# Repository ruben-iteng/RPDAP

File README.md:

<div align="center">

# RPDAP

<br/>

CMSIS-DAP debugger hardware based on a Raspberry Pi RP2040 microcontroller.

</div>

## About

This project contains the hardware designs for a RP2040 based CMSIS-DAP debugger running the [free-dap](https://github.com/ruben-iteng/free-dap) firmware.

This project is build with [atopile](https://atopile.io).

### Features

- USB interface (data and power)
- status LEDs for VCP (Virtual COM Port), DAP status, and power.
- level shifted target interface (SWD, UART)
  - 1.2-5.5V target logic voltage

#### Layouts

There are various layouts and standalone boards available:

|   |   |
|---------------------------------------|---------------------------------------|
| Basic layout without connectors (for inclusion in your own design/PCBA) | Standalone stick shaped layout with female USB Type-C, Cortex-M debug header and 4-pin JST-SH UART connector. All inside a PCB enclosure. |
|    |  |
| Standalone RPDAP Compact board (JLink Base Compact compatible board shape) |  JLink Base Compact compatible "footprint" (for using as build-in debugger/programmer) |

### Firmware

The firmware for the debugger is available in the [free-dap](https://github.com/ruben-iteng/free-dap/releases/latest) repository.
Follow this standard RP2040 flashing procedure to flash the firmware.

### Enclosures

This RPDAP Stick has a build in enclosure in the design (part of the PCB), and the RPDAP Compact board has a [3D printable enclosure](./cad/README.md) available.

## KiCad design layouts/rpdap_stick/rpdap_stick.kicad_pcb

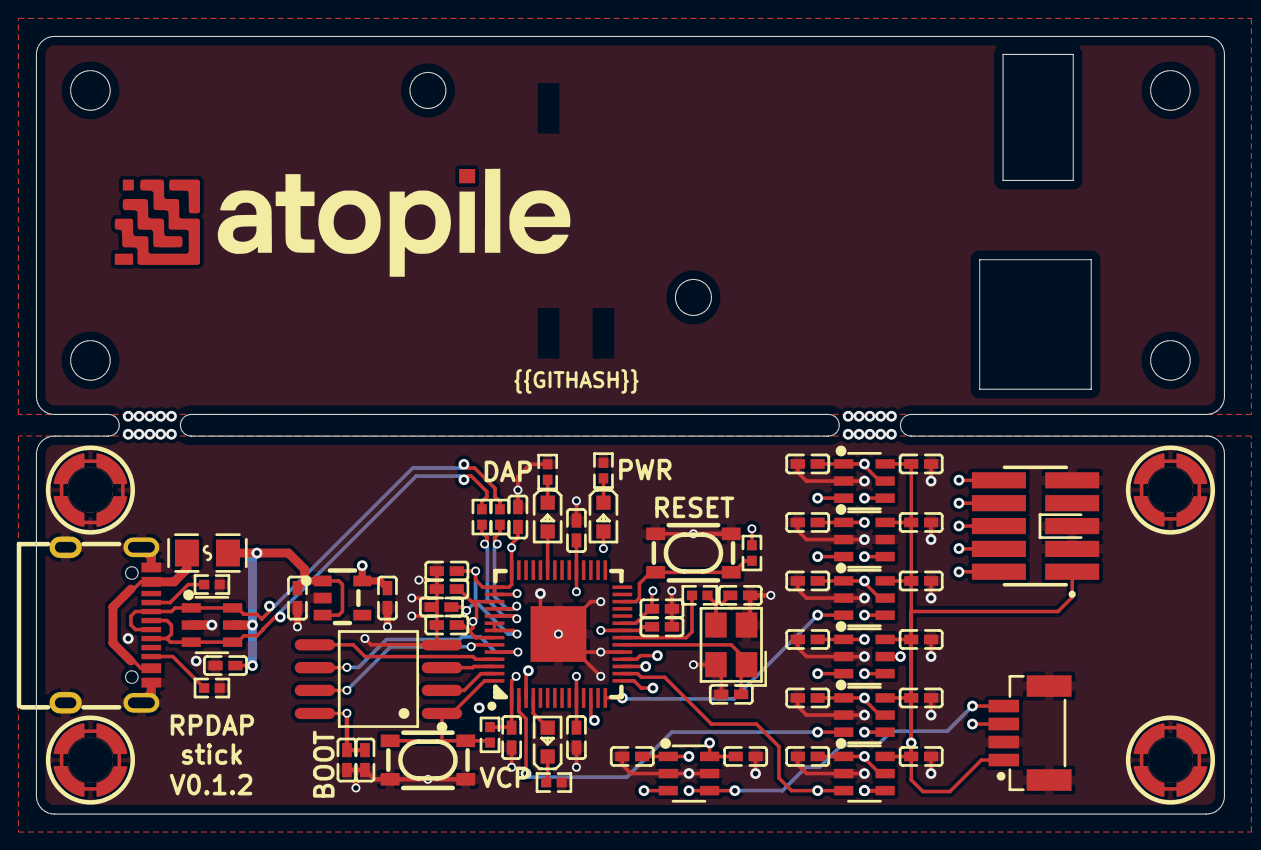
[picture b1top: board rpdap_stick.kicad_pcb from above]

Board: 4 copper layers, 66.0 x 43.2 mm, 67 parts (0 on the bottom side), 42 nets.

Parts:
C1, C2, C3, C4, C5, C6, C7, C8, C9, C10, C11, C12, C13, C14, C15, C16, C18, C19, C23, C24, C25, C26, C27, C28, C30, C31: 100nF ±10% 16V X7R; C0402
C17, C22, C29: 2.2µF ±10% 16V X5R; C0402
C20, C21: 15pF ±5% 50V C0G; C0402
CN1: CONN-SMD_FTSH-105-01-L-DV-K-TR
D1: SOT-23-6_L2.9-W1.6-P0.95-LS2.8-BL
F1: F0805
LED1, LED2, LED3: LED0603-RD
LOGO1: atopile_Logo_25x6mm
R1, R3, R4, R8: 10kΩ ±1% 62.5mW; R0402
R2, R7: 1kΩ ±1% 62.5mW; R0402
R5, R6: 27Ω ±1% 62.5mW; R0402
R9, R10: 5.1kΩ ±1% 62.5mW; R0402
SW1, SW2: KEY-SMD_4P-L4.2-W3.2-P2.20-LS4.6
U1: SOT-23-5_L2.9-W1.6-P0.95-LS2.8-BR
U2, U3, U4, U5, U6, U7, U15: SOT-23-6_L2.9-W1.6-P0.95-LS2.8-BL
U8: LQFN-56_L7.0-W7.0-P0.4-EP
U9: SOIC-8_L5.3-W5.3-P1.27-LS8.0-BL
U10: CONN-SMD_4P-P1.00_HC-1.0-4PLT
U11, U12, U13, U14: SMD_BD3.2-D2.4
USB1: USB-C-SMD_TYPE-C-6PIN-2MD-073
X1: CRYSTAL-SMD_4P-L3.2-W2.5-BL

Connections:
3V3: C2.1, C3.1, C5.1, C7.1, C9.1, C11.1, C13.1, C15.1, C22.1, C23.1, C24.1, C25.1, C26.1, C27.1, C28.1, C29.1, C30.1, LED2.2, R1.2, R4.2, U1.5, U2.1, U3.1, U3.5, U4.1, U5.1, U5.5, U6.1, U6.5, U7.1, U7.5, U8.1, U8.10, U8.22, U8.33, U8.42, U8.43, U8.44, U8.48, U8.49, U9.8, U15.1
DIR: U2.5, U8.12
GND: C1.2, C2.2, C3.2, C4.2, C5.2, C6.2, C7.2, C8.2, C9.2, C10.2, C11.2, C12.2, C13.2, C14.2, C15.2, C16.2, C17.2, C18.2, C19.2, C20.2, C21.2, C22.2, C23.2, C24.2, C25.2, C26.2, C27.2, C28.2, C29.2, C30.2, C31.2, CN1.3, CN1.5, CN1.9, D1.2, R3.1, R7.2, R8.2, R9.2, R10.2, SW1.3, SW1.4, SW2.3, SW2.4, U1.2, U2.2, U3.2, U4.2, U4.5, U5.2, U6.2, U7.2, U8.19, U8.57, U9.4, U10.2, U10.5, U10.6, U11.1, U12.1, U13.1, U14.1, U15.2, U15.5, USB1.1, USB1.12, USB1.13, USB1.14, USB1.15, USB1.16, X1.2, X1.4
K: LED1.1, R3.2
RUN: R4.1, SW2.1, SW2.2, U8.26
TCK_SWCLK: CN1.4, U3.4
TDI: CN1.8, U6.4
TDO_SWO: CN1.6, U4.4
TMS_DIO: CN1.2, U2.4
Vbus_fused: C1.1, C31.1, D1.5, F1.2, U1.1, U1.3
XIN: C20.1, U8.20, X1.1
XOUT: R2.2, U8.21
_core_regulator_out_power-VCC: C17.1, C18.1, C19.1, U8.23, U8.45, U8.50
anode: LED3.2, U8.4
cc[0]-line: R9.1, USB1.4
cc[1]-line: R10.1, USB1.10
chip_select: R1.1, SW1.1, SW1.2, U8.56, U9.1
clock: U8.52, U9.6
data_0: U8.53, U9.5
data_1: U8.55, U9.2
data_2: U8.54, U9.3
data_3: U8.51, U9.7
footprint-cathode-0: LED2.1, R7.1
footprint-cathode-1: LED3.1, R8.1
gpio[11]-A: U3.3, U8.14
gpio[12]-A: U2.3, U8.15
gpio[13]-A: U6.3, U8.16
gpio[14]-A: U4.3, U8.17
gpio[15]-A: U5.3, U8.18
input-A: LED1.2, U8.37
input-USB_D_N: D1.1, D1.6, R6.1, USB1.5, USB1.7
input-USB_D_P: D1.3, D1.4, R5.1, USB1.6, USB1.8
mcu-uart-RX: U8.3, U15.3
mcu-uart-TX: U7.3, U8.2
nRESET: CN1.10, U5.4
output: C21.1, R2.1, X1.3
output-USB_D_N: R6.2, U8.46
output-USB_D_P: R5.2, U8.47
power_vbus-VCC: F1.1, USB1.2, USB1.11
reference-VCC: C4.1, C6.1, C8.1, C10.1, C12.1, C14.1, C16.1, CN1.1, U2.6, U3.6, U4.6, U5.6, U6.6, U7.6, U10.1, U15.6
uart_connector-uart-RX: U10.4, U15.4
uart_connector-uart-TX: U7.4, U10.3

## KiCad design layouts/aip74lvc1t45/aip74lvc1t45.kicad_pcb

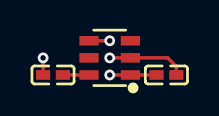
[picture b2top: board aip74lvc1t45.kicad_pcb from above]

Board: 2 copper layers, 3 parts (0 on the bottom side), 3 nets.

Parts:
C1, C2: 100nF ±10% 16V X7R; C0402
U1: SOT-23-6_L2.9-W1.6-P0.95-LS2.8-BL

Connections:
GND: C1.2, C2.2, U1.2
power_a-VCC: C1.1, U1.1
power_b-VCC: C2.1, U1.6

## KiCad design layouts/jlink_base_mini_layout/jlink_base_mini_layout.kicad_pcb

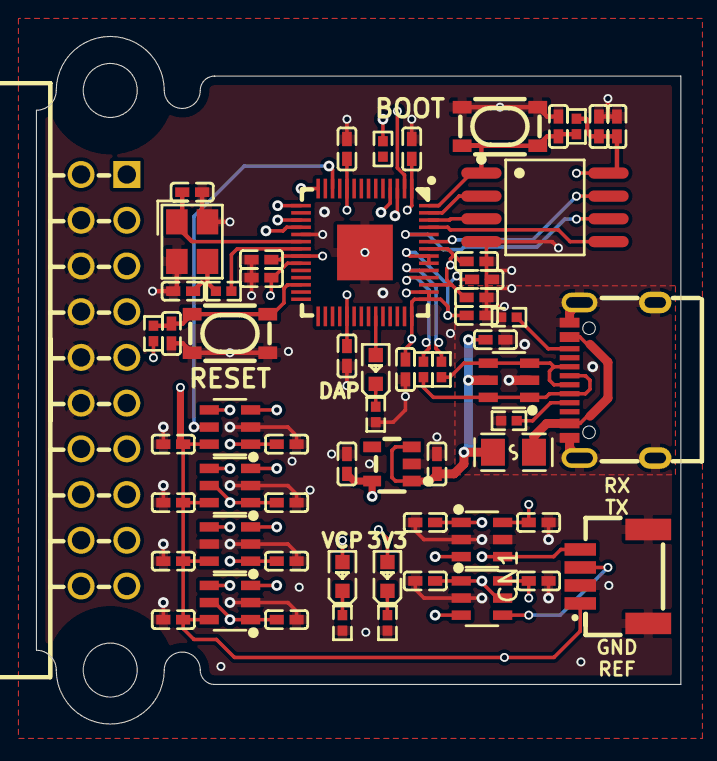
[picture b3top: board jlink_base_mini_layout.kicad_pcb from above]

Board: 4 copper layers, 35.8 x 38.2 mm, 62 parts (0 on the bottom side), 40 nets.

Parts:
C1, C2, C3, C4, C5, C6, C7, C8, C9, C10, C11, C12, C13, C14, C17, C18, C22, C23, C24, C25, C26, C27, C29, C31: 100nF ±10% 16V X7R; C0402
C15, C30: 1µF ±10% 25V X5R; C0402
C16, C21, C28: 2.2µF ±20% 6.3V X5R; C0402
C19, C20: 15pF ±5% 50V C0G; C0402
CN1: CONN-SMD_4P-P1.00_HCTL_HC-1.0-4PWT
D1: SOT-23-6_L2.9-W1.6-P0.95-LS2.8-BL
F1: F0805
LED1, LED2, LED3: LED0603-RD
R1, R4: 1kΩ ±1% 62.5mW; R0402
R2: 100kΩ ±1% 62.5mW; R0402
R3, R5, R6, R11: 10kΩ ±1% 62.5mW; R0402
R7, R8: 27Ω ±1% 62.5mW; R0402
R9, R10: 5.1kΩ ±1% 62.5mW; R0402
SW1, SW2: KEY-SMD_4P-L4.2-W3.2-P2.20-LS4.6
U1: IDC-TH_20P-P2.54_ZX-IDC2.54-2-10PWZ
U2: SOT-23-5_L2.9-W1.6-P0.95-LS2.8-BR
U3, U4, U5, U6, U7, U8: SOT-23-6_L2.9-W1.6-P0.95-LS2.8-BL
U9: LQFN-56_L7.0-W7.0-P0.4-EP
U10: SOIC-8_L5.3-W5.3-P1.27-LS8.0-BL
USB1: USB-C-SMD_TYPE-C-6PIN-2MD-073
X1: CRYSTAL-SMD_4P-L3.2-W2.5-BL

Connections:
3V3: C2.1, C3.1, C5.1, C7.1, C9.1, C11.1, C13.1, C21.1, C22.1, C23.1, C24.1, C25.1, C26.1, C27.1, C28.1, C29.1, LED1.2, R2.2, R3.1, R6.1, U2.5, U3.1, U4.1, U4.5, U5.1, U6.1, U6.5, U7.1, U7.5, U8.1, U9.1, U9.10, U9.22, U9.33, U9.42, U9.43, U9.44, U9.48, U9.49, U10.8
-hv: C4.1, C6.1, C8.1, C10.1, C12.1, C14.1, CN1.1, U1.1, U3.6, U4.6, U5.6, U6.6, U7.6, U8.6
A: LED2.2, U9.37
DI: U9.53, U10.5
DO: U9.55, U10.2
DVDD: C16.1, C17.1, C18.1, U9.23, U9.45, U9.50
GND: C1.2, C2.2, C3.2, C4.2, C5.2, C6.2, C7.2, C8.2, C9.2, C10.2, C11.2, C12.2, C13.2, C14.2, C15.2, C16.2, C17.2, C18.2, C19.2, C20.2, C21.2, C22.2, C23.2, C24.2, C25.2, C26.2, C27.2, C28.2, C29.2, C30.2, C31.2, CN1.2, CN1.5, CN1.6, D1.2, R1.2, R5.1, R9.2, R10.2, R11.2, SW1.1, SW1.2, SW2.1, SW2.2, U1.4, U1.6, U1.8, U1.10, U1.12, U2.2, U3.2, U4.2, U5.2, U5.5, U6.2, U7.2, U8.2, U8.5, U9.19, U9.57, U10.4, USB1.1, USB1.12, USB1.13, USB1.14, USB1.15, USB1.16, X1.2, X1.4
K: LED2.1, R5.2
QSPI_SCLK: U9.52, U10.6
QSPI_SD2: U9.54, U10.3
QSPI_SD3: U9.51, U10.7
QSPI_SS: C15.1, R3.2, SW1.3, SW1.4, U9.56, U10.1
RP_USB_N: R8.2, U9.46
RP_USB_P: R7.2, U9.47
RUN: C30.1, R6.2, SW2.3, SW2.4, U9.26
TARGET_RESET: U1.15, U6.4
TARGET_SWCLK: U1.9, U4.4
TARGET_SWDIO: U1.7, U3.4
TARGET_SWO: U1.13, U5.4
TARGET_UART_RX: CN1.4, U8.4
TARGET_UART_TX: CN1.3, U7.4
USB_N: D1.1, D1.6, R8.1, USB1.5, USB1.7
USB_P: D1.3, D1.4, R7.1, USB1.6, USB1.8
VBUS: C1.1, C31.1, D1.5, F1.2, U1.19, U2.1, U2.3
anode: LED3.2, U9.4
cathode-0: LED1.1, R1.1
cathode-1: LED3.1, R11.1
hv: F1.1, USB1.2, USB1.11
line-0: R9.1, USB1.4
line-1: R10.1, USB1.10
output: C20.1, R4.1, X1.3
rpdap-line-0: U3.3, U9.15
rpdap-line-1: U3.5, U9.12
rpdap-line-2: U4.3, U9.14
rpdap-line-3: U5.3, U9.17
rpdap-line-4: U6.3, U9.18
rpdap-line-5: U7.3, U9.2
rpdap-line-6: U8.3, U9.3
xin: C19.1, U9.20, X1.1
xout: R4.2, U9.21

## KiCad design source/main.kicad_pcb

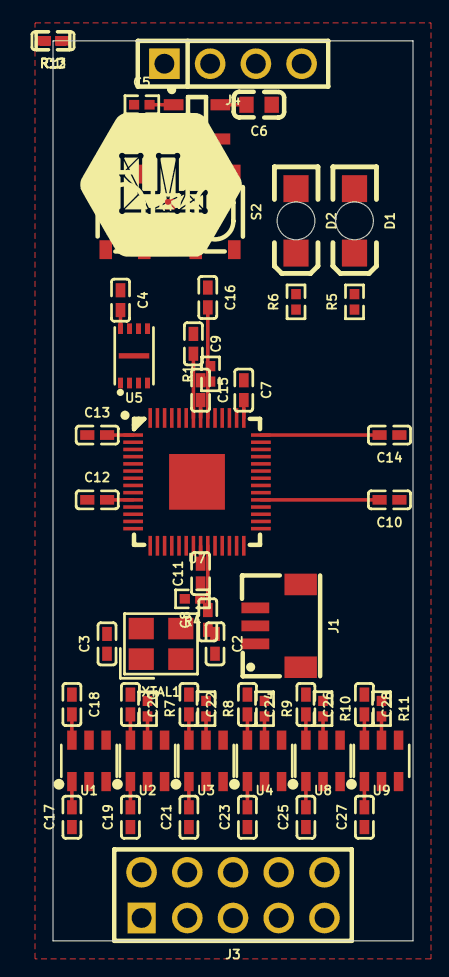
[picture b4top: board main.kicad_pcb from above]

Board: 2 copper layers, 20.0 x 50.0 mm, 59 parts (1 on the bottom side), 35 nets.

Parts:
C1, C4, C7, C8, C9, C10, C11, C12, C13, C14, C15, C16, C17, C18, C19, C20, C21, C22, C23, C24, C25, C26, C27, C28: 100nF 16V X7R; C0402
C2, C3: 18pF ±5% 50V C0G; C0402
C5: 10µF 25V X5R; R0402
C6: 10µF 10V X7R; C0603
D1, D2: 3.05V; LED-SMD_L3.2-W1.3-RD_GREEN-MHT151UGCT
J1: PICO_DebugHeader; CONN-SMD-3P-P1.00_BM03B-SRSS-TB-LF-SN
J3: Header; HDR-TH_10P-P2.54-V-F-R2-C5-S2.54
J4: Header; HDR-TH_4P-P2.54-V-F
LOGO1: faebrykLogo; faebryk_logo
R1, R7, R8, R9, R10, R11, R13: 10kΩ ±1% 62.5mW; R0402
R2, R3, R4, R5, R6: 1kΩ ±1% 62.5mW; R0402
R12: 100Ω ±1% 62.5mW; R0402
S1, S2: _Switch; KEY-SMD_4P-L4.2-W3.2-P2.20-LS4.6
U1, U2, U3, U4, U8, U9: Wuxi_I_core_Elec_AiP74LVC1T45GB236_TR; SOT-23-6_L2.9-W1.6-P0.95-LS2.8-BL
U5: Winbond_W25Q16JVUXIQ; USON-8_L3.0-W2.0-P0.50-BL-EP
U6: LDO 3.3V 600mA 400mV Vin max 6V Iq 80µA; SOT-25-5_L2.9-W1.6-P0.95-LS2.8-BL
U7: RP2040; LQFN-56_L7.0-W7.0-P0.4-EP
XTAL1: Crystal; CRYSTAL-SMD_4P-L3.2-W2.5-BL

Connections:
3V3: C4.1, C6.1, C10.1, C11.1, C12.1, C13.1, C14.1, C15.1, C16.1, C17.1, C19.1, C21.1, C23.1, C25.1, C27.1, D1.2, D2.2, R2.2, R7.2, R9.2, R11.2, R13.2, U1.1, U2.1, U3.1, U4.1, U5.8, U6.5, U7.1, U7.10, U7.22, U7.33, U7.42, U7.44, U7.48, U7.49, U8.1, U9.1
C2-1-R4-1-XTAL1-4: C2.1, R4.1, XTAL1.4
C2-2-C3-2-XTAL1-1: C2.2, C3.2, XTAL1.1
C3-1-U7-19-XTAL1-2: C3.1, U7.19, XTAL1.2
C7-1-U7-43: C7.1, U7.43
C8-1-C9-1-U7-23-U7-45-U7-50: C8.1, C9.1, U7.23, U7.45, U7.50
D1-1-R5-1: D1.1, R5.1
D2-1-R6-1: D2.1, R6.1
GND: C4.2, C5.2, C6.2, C7.2, C8.2, C9.2, C10.2, C11.2, C12.2, C13.2, C14.2, C15.2, C16.2, C17.2, C18.2, C19.2, C20.2, C21.2, C22.2, C23.2, C24.2, C25.2, C26.2, C27.2, C28.2, J1.2, J3.3, J4.4, R5.2, R6.2, R8.2, R10.2, S1.3, S2.2, U1.2, U2.2, U3.2, U4.2, U5.4, U5.9, U6.2, U7.57, U8.2, U9.2
GND_DETECT: J3.9, R12.2
J1-1-U7-25: J1.1, U7.25
J1-3-U7-24: J1.3, U7.24
R2-1-R3-1-U5-1-U7-56: R2.1, R3.1, U5.1, U7.56
R3-2-S1-1: R3.2, S1.1
R4-2-U7-20: R4.2, U7.20
R7-1-U2-5: R7.1, U2.5
R8-1-U3-5: R8.1, U3.5
R9-1-U4-5: R9.1, U4.5
R10-1-U8-5: R10.1, U8.5
R11-1-U9-5: R11.1, U9.5
R12-1-R13-1: R12.1, R13.1
S2-1-U7-26: S2.1, U7.26
SWD_CLK: J3.4, U2.4
SWD_DIO: J3.2, U1.4
SWD_RESET: J3.10, U4.4
SWD_SWO: J3.6, U3.4
U5-2-U7-55: U5.2, U7.55
U5-3-U7-54: U5.3, U7.54
U5-5-U7-53: U5.5, U7.53
U5-6-U7-52: U5.6, U7.52
U5-7-U7-51: U5.7, U7.51
UART_RX: J3.5, U9.4
UART_TX: J3.7, U8.4
VBUS: C5.1, J4.1, U6.1, U6.3
VTARGET: C18.1, C20.1, C22.1, C24.1, C26.1, C28.1, J3.1, U1.6, U2.6, U3.6, U4.6, U8.6, U9.6

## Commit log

2022-12-30 Initial commit
    Strip down SSO from Ruben.
    Replace references with placeholders.
    Fix some typos etc.
2022-12-30 Add pre-commit
2022-12-30 gitignore: More generic kicad filter
2022-12-30 gitignore: filter .local
2024-01-29 Update to newest faebryk & Improve
    Improve boilerplate & examples.
    Update & improvove readme & installation instructions.
    Add kicad empty files (with lcsc & logo lib).
    Make appropriate folder structure.
2024-01-29 README: static faebryk version
2024-08-12 Update template files for faebryk 3.0.x (#1)
2024-08-13 Make the project template user friendly (#5)
    * Split README
    * Update faebryk api & Templates
    * Add TEMPLATE_VAR to licence
    Remove unused visual
    * Use parseable project version
    * Update placeholder image
2024-08-14 Dependencies: Update (#7)
2024-08-25 Init repository
2024-10-15 Add: basic design
2025-08-12 Update gitignore to exclude atopile and AI files
2025-08-13 add various pre-commit-hooks
2025-08-13 remove old files
2025-08-13 Add new design files
2025-08-13 add parts folder
2025-08-14 update layouts and add jlink base compact layout
2025-08-14 remove din variant
2025-08-14 refactor jlink connector, make stick prety
2025-08-15 refactor debug-connectors, fix issues in layout and connections
2025-08-15 fix stick layout
2025-08-16 rebuild, small fixes, update README
2025-08-16 Add build workflow (on version tag)
2025-08-16 Merge pull request #1 from ruben-iteng/feature/upgrade_to_ato_0_11_x
    Update to ato 0.11.x
2025-08-31 rebuild with upstream rp2040 fixes. move header .25mm to the right. center dap-LED
2025-08-31 fix workflow triggers
2025-10-16 fix swapped jlink connector pinout + update deps
2025-10-16 pin atopile workflow version to v1.x.x
2025-10-16 fix: Update deps, swapped pinout (#2)
    * rebuild with upstream rp2040 fixes. move header .25mm to the right. center dap-LED
    * fix workflow triggers
    * fix swapped jlink connector pinout + update deps
    * pin atopile workflow version to v1.x.x
2025-10-16 feat(3D): Add enclosure CAD files
2025-10-16 feat(3D): Add enclosure CAD files (#3)

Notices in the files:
README.md:
License: MIT
